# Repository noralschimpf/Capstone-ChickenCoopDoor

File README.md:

# Capstone-ChickenCoopDoor
Software and Documentation Repo for the Team 2 Capstone

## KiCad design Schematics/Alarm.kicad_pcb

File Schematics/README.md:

# Schematics
Complete schematic folder will be uploaded here. Schematic covers both the main door and wireless alarm as separate pages.

## Software Required
Project is made in KiCAD

## Accessing Project
Download the entire folder to a local location. With a running instance of KiCAD, open the schematic file from the folder

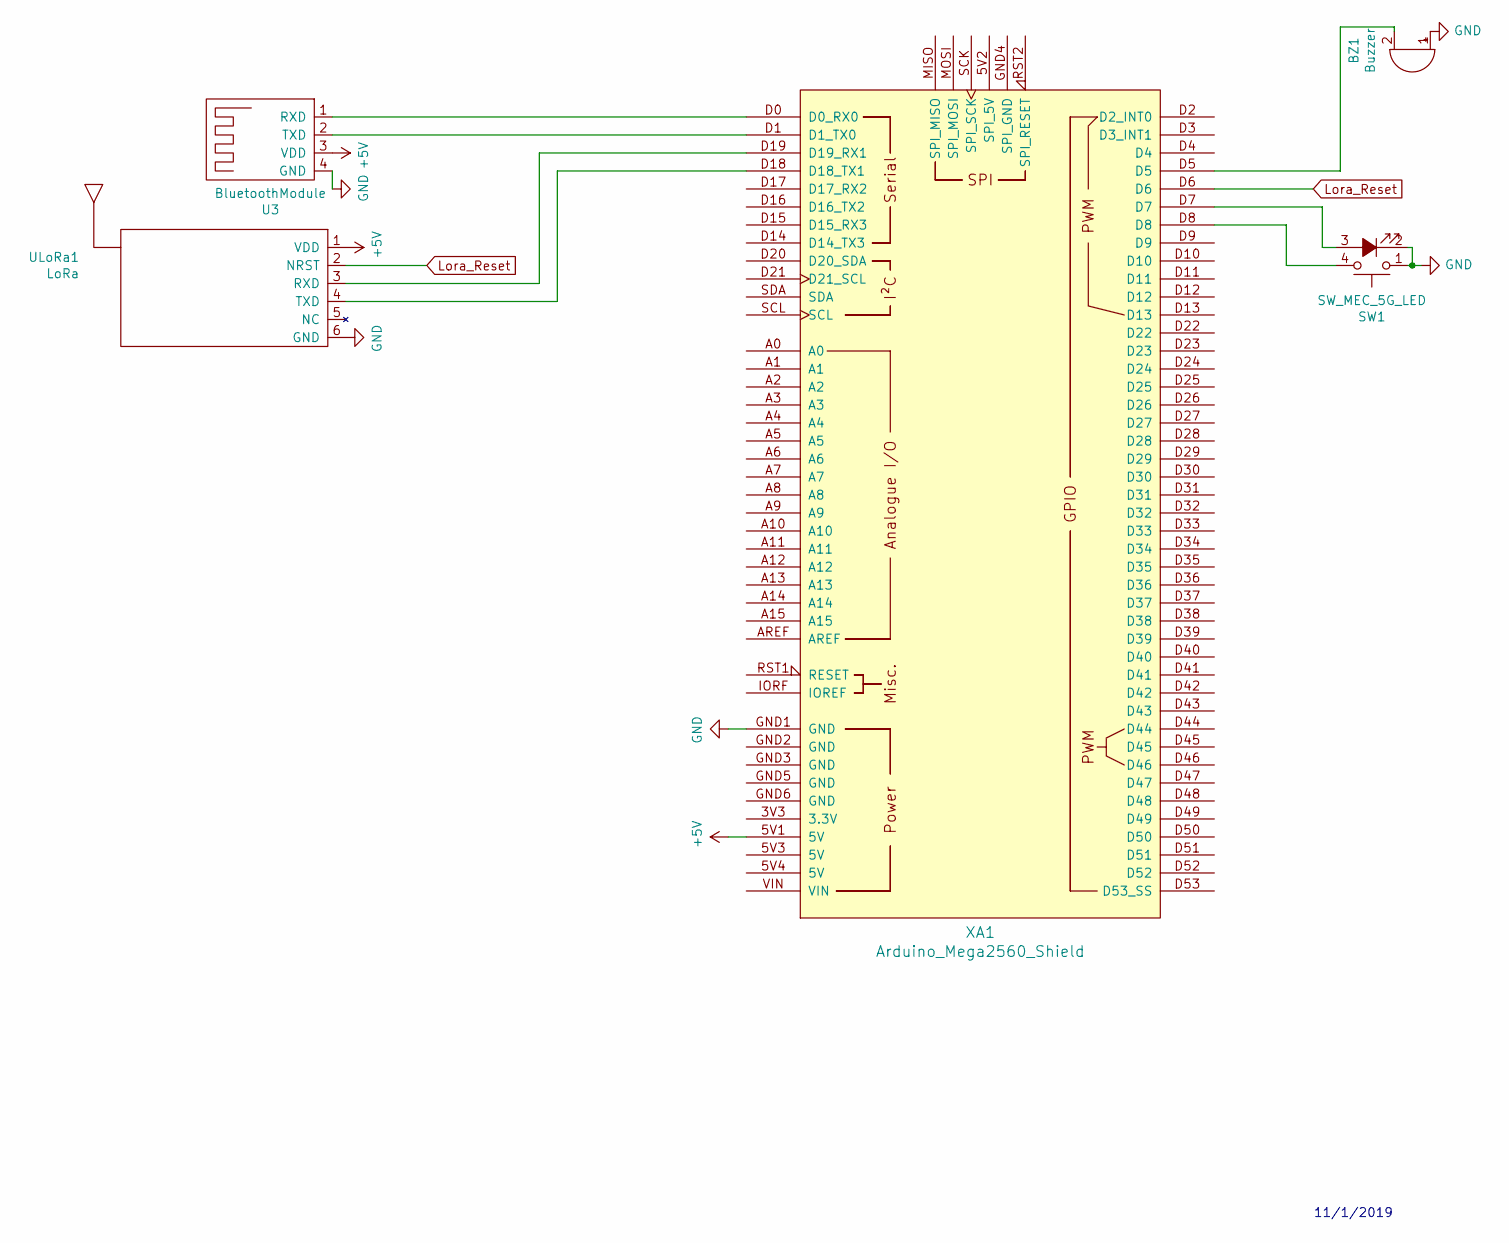
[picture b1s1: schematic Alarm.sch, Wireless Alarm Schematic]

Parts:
BZ1: Buzzer; Buzzer_15x7.5RM7.6
SW1: SW_MEC_5G_LED; Button
U3: BluetoothModule; PinSocket_1x04_P2.54mm_Horizontal
ULoRa1: LoRa; PinSocket_1x06_P2.54mm_Horizontal
XA1: Arduino_Mega2560_Shield

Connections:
+5V: U3.3 (VDD), ULoRa1.1 (VDD), XA1.5V1 (5V)
GND: BZ1.1 (-), SW1.1, SW1.2, U3.4 (GND), ULoRa1.6 (GND), XA1.GND1 (GND)
Lora_Reset: ULoRa1.2 (NRST), XA1.D6
unnamed: BZ1.2 (+), XA1.D5
unnamed: SW1.3 (K), XA1.D7
unnamed: SW1.4 (A), XA1.D8
unnamed: U3.1 (RXD), XA1.D0 (D0_RX0)
unnamed: U3.2 (TXD), XA1.D1 (D1_TX0)
unnamed: ULoRa1.3 (RXD), XA1.D19 (D19_RX1)
unnamed: ULoRa1.4 (TXD), XA1.D18 (D18_TX1)

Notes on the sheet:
11/1/2019

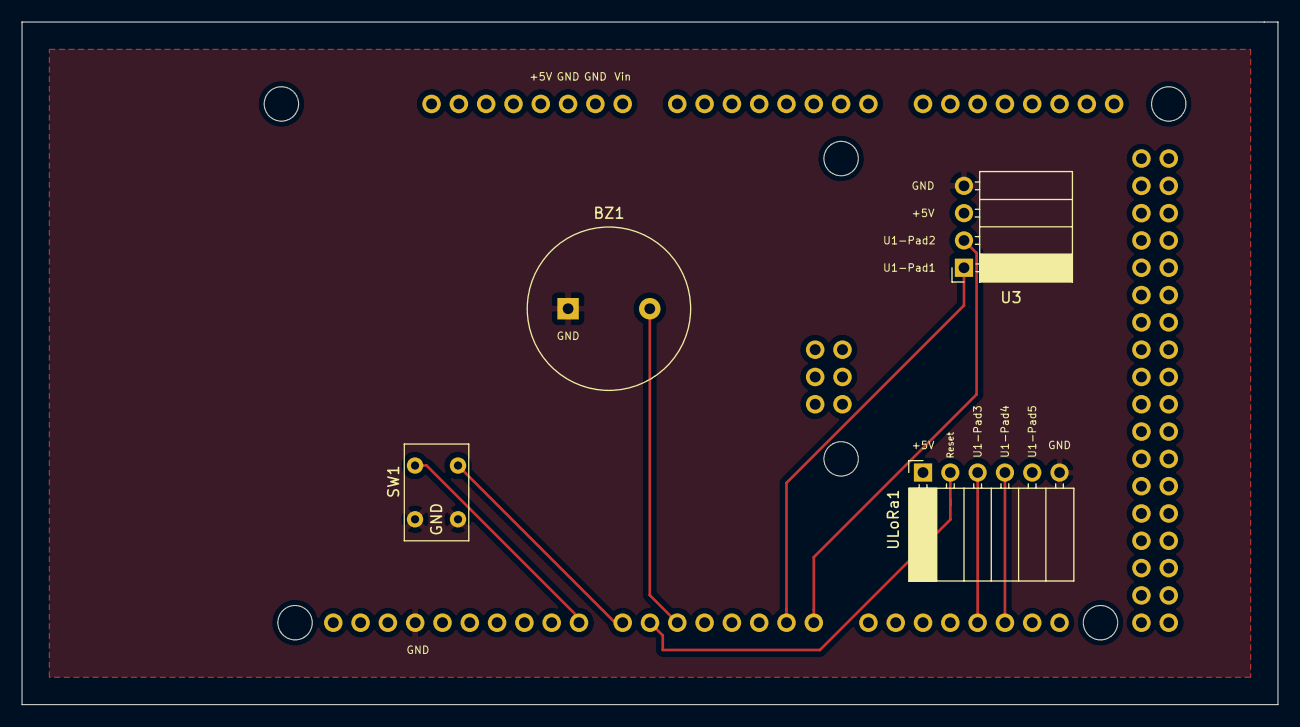
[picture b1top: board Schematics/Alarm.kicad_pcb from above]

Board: 2 copper layers, 116.8 x 63.5 mm, 5 parts (1 on the bottom side), 10 nets.

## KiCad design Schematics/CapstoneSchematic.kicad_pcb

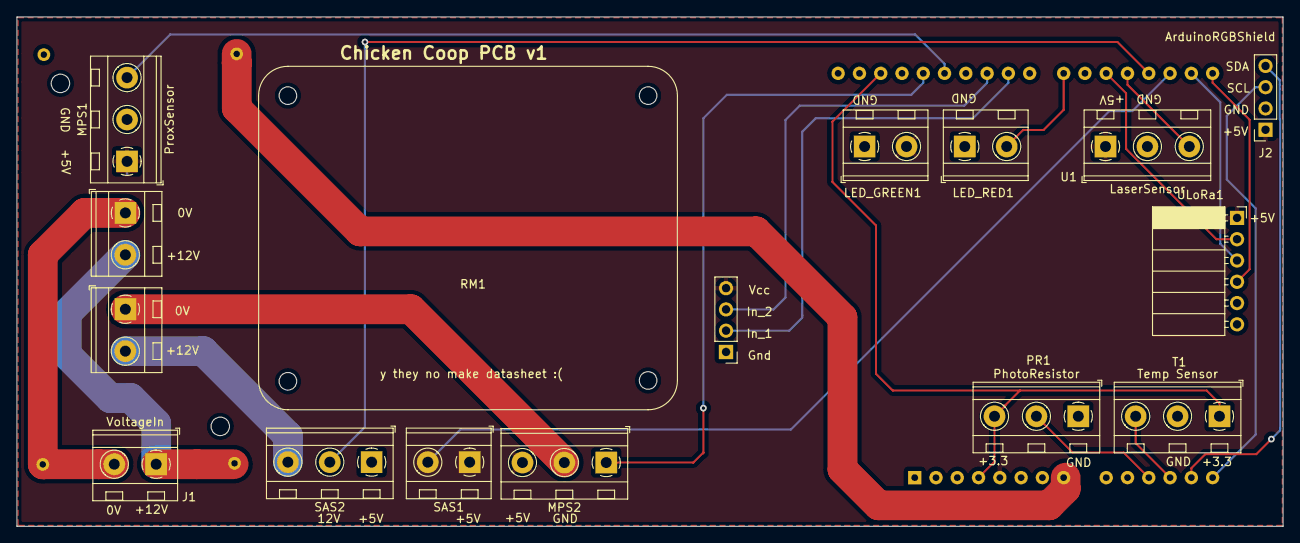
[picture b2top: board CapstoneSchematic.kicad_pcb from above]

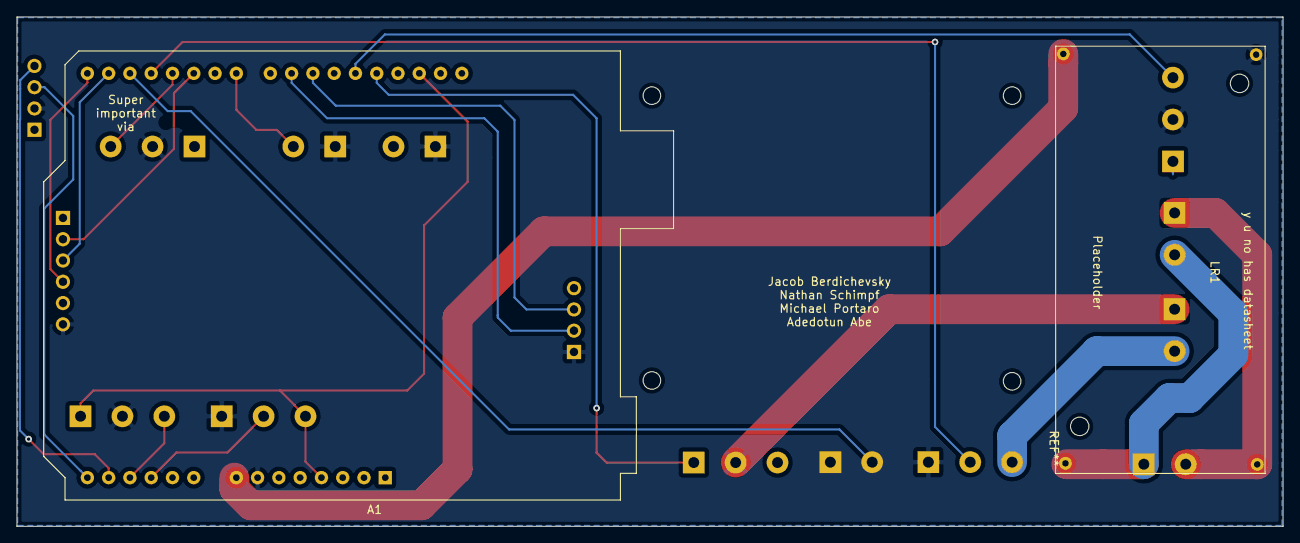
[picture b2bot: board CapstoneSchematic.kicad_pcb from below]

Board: 2 copper layers, 151.1 x 60.8 mm, 15 parts (2 on the bottom side), 21 nets.

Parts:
A1: Arduino_UNO_R3
J1: VoltageIn; TerminalBlock_MetzConnect_Type094_RT03502HBLU_1x02_P5.00mm_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
J2: ArduinoRGBShield; PinSocket_1x04_P2.54mm_Vertical
LED_GREEN1: 200; TerminalBlock_MetzConnect_Type094_RT03502HBLU_1x02_P5.00mm_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
LED_RED1: 200; TerminalBlock_MetzConnect_Type094_RT03502HBLU_1x02_P5.00mm_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
LR1: Linear_Regulator; Linear Regulator
MPS1, MPS2: ProxSensor; TerminalBlock_MetzConnect_Type094_RT03503HBLU_1x03_P5.00mm_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
PR1: PhotoResistor; TerminalBlock_MetzConnect_Type094_RT03503HBLU_1x03_P5.00mm_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
RM1: 2RelayModule; 2 Channels Relay
SAS1: SnapActionSwitch; TerminalBlock_MetzConnect_Type094_RT03502HBLU_1x02_P5.00mm_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
SAS2: SnapActionSwitch; TerminalBlock_MetzConnect_Type094_RT03503HBLU_1x03_P5.00mm_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
T1: Temp Sensor; TerminalBlock_MetzConnect_Type094_RT03503HBLU_1x03_P5.00mm_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
U1: LaserSensor; TerminalBlock_MetzConnect_Type094_RT03503HBLU_1x03_P5.00mm_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
ULoRa1: LoRa; PinSocket_1x06_P2.54mm_Horizontal

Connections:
0: J1.2, LR1.2, RM1.8
+3V3: A1.4, A1.30, PR1.3, T1.4
+5V: A1.5, J2.1, LED_GREEN1.2, MPS1.1, MPS2.1, RM1.4, U1.1, ULoRa1.1
+12V: J1.1, LR1.1, RM1.10
/IN1: A1.24, RM1.2
/IN2: A1.25, RM1.3
/LED_R: A1.22, LED_RED1.2
/LoRa2: A1.20, ULoRa1.2
/SAS_Int1: A1.17, SAS1.4
/SAS_Int2: A1.18, SAS2.2
GND: A1.7, J2.2, LED_GREEN1.1, LED_RED1.1, LR1.4, MPS1.2, PR1.1, RM1.1, SAS1.1, SAS2.1, T1.2, U1.2, ULoRa1.6
unnamed: A1.8, LR1.3
unnamed: A1.11, PR1.2
unnamed: A1.12, T1.3
unnamed: A1.13, J2.4
unnamed: A1.14, J2.3
unnamed: A1.19, U1.3
unnamed: A1.27, MPS1.3
unnamed: A1.28, MPS2.3
unnamed: RM1.9, SAS2.4
unnamed: MPS2.2, RM1.6

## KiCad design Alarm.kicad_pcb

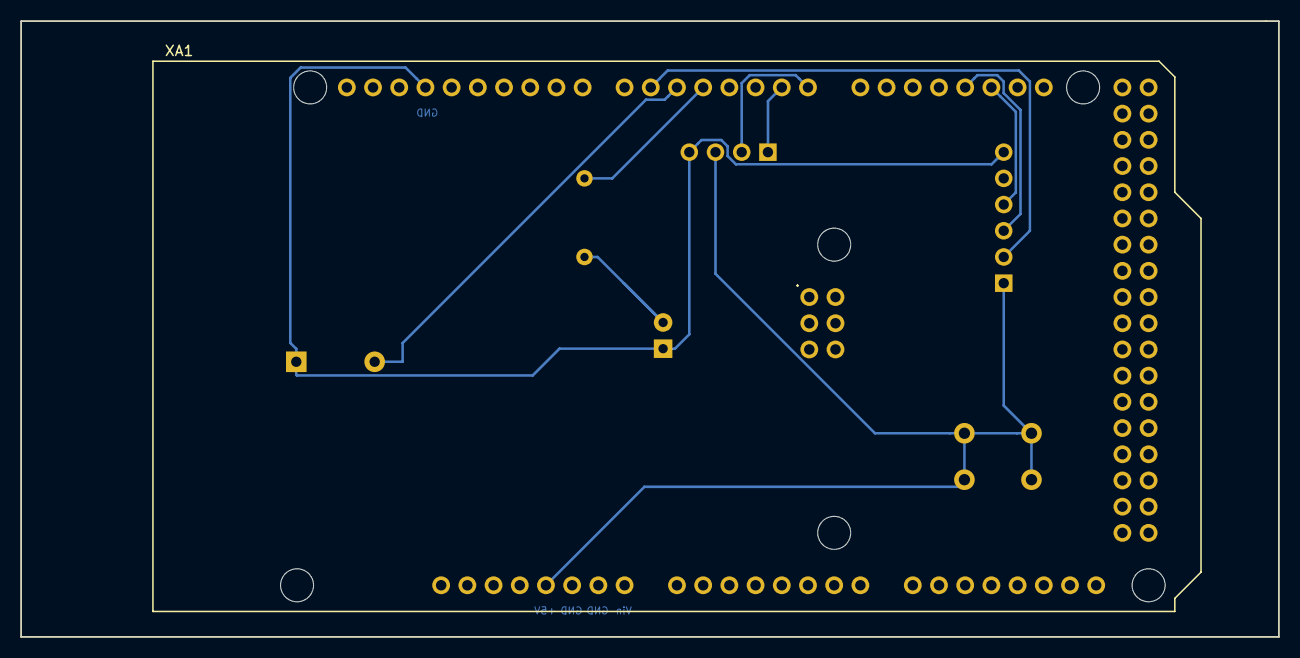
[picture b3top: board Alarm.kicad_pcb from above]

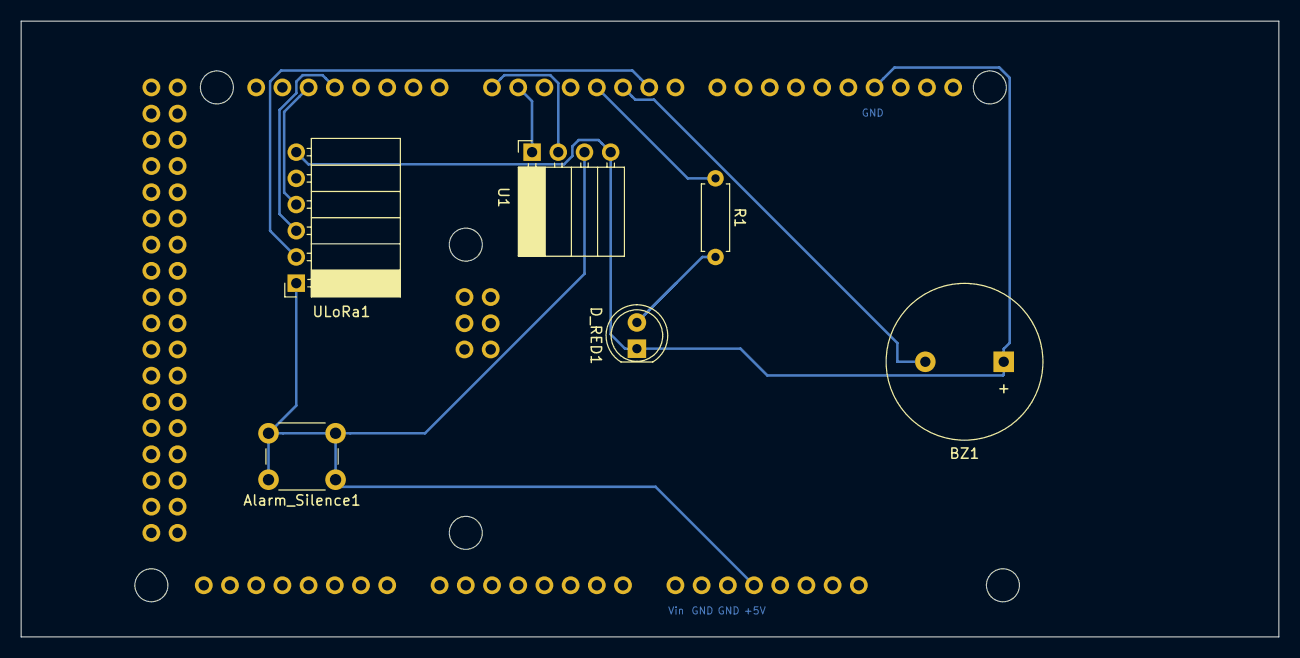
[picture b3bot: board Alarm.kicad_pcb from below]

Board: 2 copper layers, 121.9 x 59.7 mm, 7 parts (6 on the bottom side), 10 nets.

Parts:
Alarm_Silence1: SW_MEC_5G; SW_PUSH_6mm
BZ1: Buzzer; Buzzer_15x7.5RM7.6
D_RED1: LED; LED_D5.0mm
R1: 220; R_Axial_DIN0207_L6.3mm_D2.5mm_P7.62mm_Horizontal
U1: BluetoothModule; PinSocket_1x04_P2.54mm_Horizontal
ULoRa1: LoRa; PinSocket_1x06_P2.54mm_Horizontal
XA1: Arduino_Mega2560_Shield

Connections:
+5V: Alarm_Silence1.1, Alarm_Silence1.2, U1.3, ULoRa1.1, XA1.5V1
GND: BZ1.1, D_RED1.1, U1.4, ULoRa1.6, XA1.GND1
Lora_Reset: ULoRa1.2, XA1.D6
unnamed: BZ1.2, XA1.D5
unnamed: D_RED1.2, R1.2
unnamed: R1.1, XA1.D4
unnamed: U1.1, XA1.D1
unnamed: U1.2, XA1.D0
unnamed: ULoRa1.3, XA1.D18
unnamed: ULoRa1.4, XA1.D19

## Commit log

2019-10-30 Update README.md
    Fixed header markdown
2019-10-30 Update README.md
    Added Alarms.c
2019-11-05 adding nathan and abe's changes
2019-11-06 Added Door Obstruction sensor
2019-11-06 Initial Flowcharts
2019-11-09 Did main pcb
2019-11-09 Fixed the project
2019-11-09 Fixed better
2019-11-09 Started routing
2019-11-10 finished pcb
2019-11-10 Fixed a layer
2019-11-10 Main menu progress
2019-11-14 Emergency fix
2019-11-16 Added flowchart and latest gerbers
2019-11-17 Match to C++ guidelines
2019-11-19 Following C++ Guidelines
    Added Include Guards, redefined as struct
2019-11-19 Constant Parameter Definitions
    Provide a global location for adjusting sensor values, Arduino pin references, etc.
2019-11-20 C++ Guidelines
    Broke Settings.h into respective header/source files; added include guards; fleshed out methods for object construction, accessing, and modifying.
2019-11-20 Added Settings Full-Constructor
2019-11-20 Constructor Prototypes missing
2019-12-01 Menu and ADCs
    MISSING:
    ADC Decision Making,
    Scrolling Support
    Safety inputs
2019-12-01 Menu Scrolling and ADC operation
    Day/Night Mode transition to door operation on ADC
    Menu refreshes line in 16-char increments
    MISSING:
    auto-exit door operation states
    refresh displayed ADC values more frequently
2019-12-02 Jacob and Nathan working on the project
2019-12-02 UPTO: Temp readout in Fahrenheit
2019-12-02 UPTO: ADC Readout precision fits LCD
2019-12-03 Schematic: updated Titleblock and notes
2020-01-19 Trying to fix door
2020-01-19 Enclosure Model
2020-01-19 Enclosure model (Wall Attachment)
2020-01-19 Added note to schem
2020-02-09 Moved Display files to new class, transitioning to AS7
2020-02-23 Fixed repo
2020-02-23 Made things look better on wireless alarm
2020-02-24 MAIN DOOR EXECUTES - TODO: DISPLAY OBJECT SHARING
2020-02-24 UPTO: Functioning Display - TODO: SPI Interrupts
2020-03-01 Safety Class Drafting
2020-03-01 Add files via upload
    First draft of alarm PCB
2020-03-02 Fixed file organization
2020-03-11 Add files via upload
    Alarm PCB Rev 2
2020-03-15 Safety Draft
2020-03-18 Fixing folder
2020-03-22 Jacob comments
2020-03-22 Safety Drafting 1.01
2020-03-22 quick responses before meet
2020-03-23 Sensor drafting, Safety mod, Readme update
2020-03-23 Sensor Class Drafting
2020-03-23 Conformance to SDS
2020-04-05 Added Michael's alarm pcb rev
2020-04-05 Changed the leds
2020-04-09 Alarm PCB Changes
    Fixes to the text layering and traces
2020-04-12 Fixed button
2020-04-12 Nonworking code
2020-04-13 Fixed most of schematic, need to update linear regulator footprint
2020-04-15 Fixed Linear regulator footprint
2020-04-19 Added Code for door without interrupts
2020-04-19 Added temp button pcb footprint
2020-04-19 Surface Changes And Button Retracking
2020-04-20 Updated Diagrams
2020-04-22 Updated System Diagram (SDS)
2020-04-25 added comments and renamed folder
2020-04-26 Add files via upload
    CECS Capstone Project
